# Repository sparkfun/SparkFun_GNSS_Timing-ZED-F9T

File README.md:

SparkFun GNSS Timing Breakout - ZED-F9T (Qwiic)
========================================

[*SparkFun GNSS Timing Breakout - ZED-F9T (Qwiic) (GPS-18774)*](https://www.sparkfun.com/products/18774)

The SparkFun GNSS Timing Breakout - ZED-F9T (Qwiic) offers a unique entry into SparkFun&apos;s GNSS catalog featuring the ZED-F9T GNSS receiver from u-blox. The ZED-F9T provides up to 5 nanosecond timing accuracy under clear skies with no external GNSS correction. The ZED-F9T supports L1/L2 bands and operates on all major constellations concurrently so it is able to maintain its timing precision even if the module loses connection with on or more of the visible constellations.

The breakout includes a USB-C connector for primary power and communication, two Qwiic connectors for communicating over I<sup>2</sup>C using the SparkFun [Qwiic system](https://www.sparkfun.com/qwiic), three SMA connectors for the antenna and timing pulse signals as well as a host of PTH pins allowing direct interaction with most of the ZED-F9T's pinout. The board also includes an on-board rechargeable battery that provides power to the RTC on the ZED-F9T. This reduces the time-to-first fix from a cold start (~24s) to a hot start (~2s). 

Repository Contents
-------------------

* **/Documents** - Datasheet, Appnotes.
* **/Hardware** - Eagle design files (.brd, .sch)

Documentation
-------------

* **[SparkFun u-blox GNSS Arduino Library](https://github.com/sparkfun/SparkFun_u-blox_GNSS_Arduino_Library)** - A comprehensive library for all SparkFun u-blox products.
* **[Hookup Guide](https://learn.sparkfun.com/tutorials/gnss-timing-breakout---zed-f9t-qwiic-hookup-guide)** - A basic Hookup Guide to get started with the SparkFun GNSS Timing Breakout - ZED-F9T (Qwiic).

Product Versions
----------------
* [GPS-18774](https://www.sparkfun.com/products/18774) - Initial release

Version History
---------------
* v1.0 - Initial Release 

License Information
-------------------

This product is _**open source**_! 

Please review the LICENSE.md file for license information. 

If you have any questions or concerns on licensing, please contact technical support on our [SparkFun forums](https://forum.sparkfun.com/viewforum.php?f=152).

Distributed as-is; no warranty is given.

- Your friends at SparkFun.

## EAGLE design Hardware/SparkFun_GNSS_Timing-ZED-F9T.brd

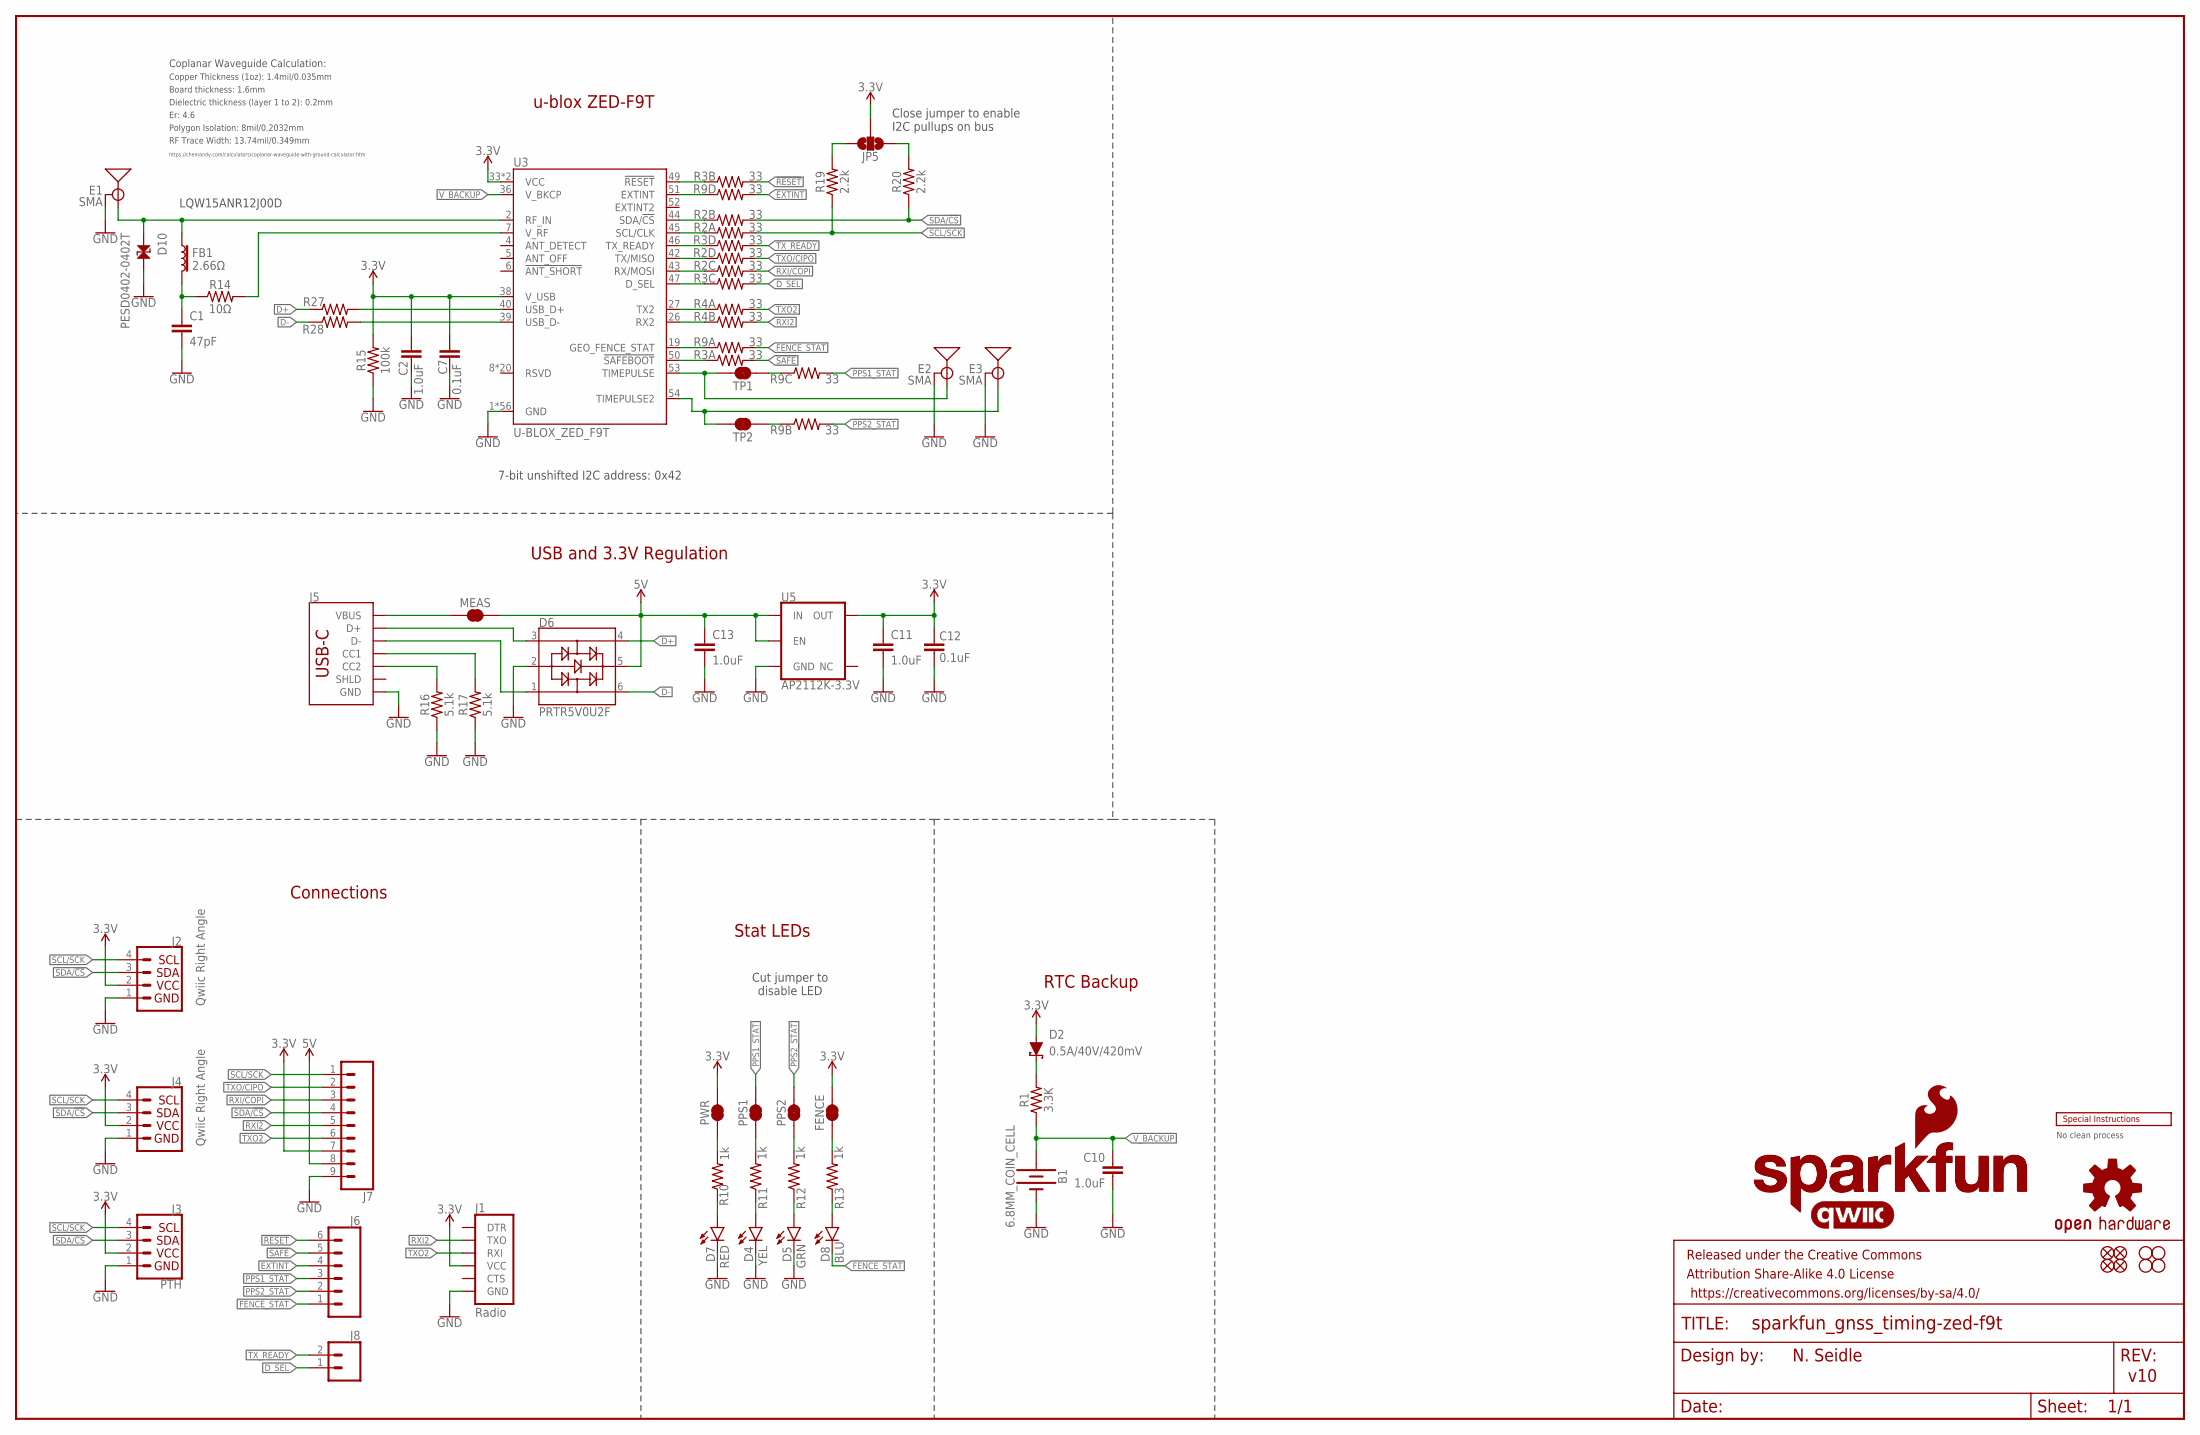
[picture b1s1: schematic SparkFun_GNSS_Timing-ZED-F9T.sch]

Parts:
B1: 6.8MM_COIN_CELL; ML414H_IV01E
C1: 47pF; 0402-TIGHT
C2, C10, C11, C13: 1.0uF; 0402-TIGHT
C7, C12: 0.1uF; 0402-TIGHT
D2: 0.5A/40V/420mV; SOD-323
D4: YEL; LED-0603
D5: GRN; LED-0603
D6: PRTR5V0U2F; SOT886
D7: RED; LED-0603
D8: BLU; LED-0603
D10: PESD0402-0402T; 0402-TIGHT
E1, E2, E3: SMA; SMA-EDGE
FB1: 2.66Ω; 0402-TIGHT
FENCE: JUMPER-SMT_2_NC_TRACE_SILK; SMT-JUMPER_2_NC_TRACE_SILK
FRAME2: FRAME-LEDGER; CREATIVE_COMMONS
H1, H2, H3, H4: STAND-OFF
J1: Radio; 1X06_NO_SILK
J2, J4: Qwiic Right Angle; JST04_1MM_RA
J3: PTH; 1X04_NO_SILK
J5: USB Female Type C Connector; USB-C-16P_4LAYER-PADS
J6: CONN_06NO_SILK_FEMALE_PTH; 1X06_NO_SILK
J7: CONN_09NO_SILK; 1X09_NO_SILK
J8: CONN_021X02_NO_SILK; 1X02_NO_SILK
JP5: JUMPER-SMT_3_NO_SILK; SMT-JUMPER_3_NO_SILK
JP21, JP61, JP71, JP81: FIDUCIALUFIDUCIAL; FIDUCIAL-MICRO
LOGO1: OSHW-LOGOMINI; OSHW-LOGO-MINI
LOGO2: SFE_LOGO_NAME_FLAME.1_INCH; SFE_LOGO_NAME_FLAME_.1
LOGO4: QWIIC_LOGO_4MM; QWIIC_4MM
LOGO5: SFE_LOGO_NAME.1_INCH; SFE_LOGO_NAME_.1
MEAS: JUMPER-COMBO_2_NC_TRACE; COMBO-JUMPER_2_NC_TRACE
PPS1, PPS2: JUMPER-SMT_2_NC_TRACE_SILK; SMT-JUMPER_2_NC_TRACE_SILK
PWR: JUMPER-SMT_2_NC_TRACE_SILK; SMT-JUMPER_2_NC_TRACE_SILK
R1: 3.3K; 0402-TIGHT
R2, R3, R4, R9: 33; 1206_RA
R10, R11, R12, R13: 1k; 0402-TIGHT
R14: 10Ω; 0402-TIGHT
R15: 100k; 0402-TIGHT
R16, R17: 5.1k; 0402-TIGHT
R19, R20: 2.2k; 0402-TIGHT
R27, R28: 27OHM; 0402-TIGHT
TP1, TP2: JUMPER-SMT_2_NC_TRACE_SILK; SMT-JUMPER_2_NC_TRACE_SILK
U3: U-BLOX_ZED_F9T; ZED-F9X
U5: AP2112K-3.3V; SOT23-5
U$2: SPECIAL_INSTRUCTIONS-ORDERING; ORDERING_INSTRUCTIONS

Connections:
3.3V: C2.1, C7.2, C11.1, C12.2, D2.A, FENCE.2, J1.4 (VCC), J2.2, J3.2 (VCC), J4.2, J7.7, JP5.2, PWR.2, R15.2, U3.33 (VCC), U3.34 (VCC), U3.38 (V_USB), U5.5 (OUT)
5V: C13.1, D6.5, J7.8, MEAS.2, MEAS.4 (2), U5.1 (IN), U5.3 (EN)
!RESET!: J6.6, R3.P7 (2)
!RESET!_LV: R3.P2 (1), U3.49 (!RESET!)
!SAFE!: J6.5, R3.P8 (2)
!SAFE!_LV: R3.P1 (1), U3.50 (!SAFEBOOT!)
ANT_VCC: C1.1, FB1.2, R14.1
CC1: J5.A5 (CC1), R17.2
CC2: J5.B5 (CC2), R16.2
D+: D6.4, R27.1
D-: D6.6, R28.1
DSEL_LV: R3.P3 (1), U3.47 (D_SEL)
D_SEL: J8.1, R3.P6 (2)
EXTINT: J6.4, R9.P5 (2)
EXTINT_LV: R9.P4 (1), U3.51 (EXTINT)
FENCE_LV: R9.P1 (1), U3.19 (GEO_FENCE_STAT)
FENCE_STAT: D8.C, J6.1, R9.P8 (2)
GND: B1.-, C1.2, C2.2, C7.1, C10.2, C11.2, C12.1, C13.2, D4.C, D5.C, D6.2, D7.C, D10.2, E1.GND@0 (GND), E1.GND@1 (GND), E1.GND@2 (GND), E1.GND@3 (GND), E2.GND@0 (GND), E2.GND@1 (GND), E2.GND@2 (GND), E2.GND@3 (GND), E3.GND@0 (GND), E3.GND@1 (GND), E3.GND@2 (GND), E3.GND@3 (GND), J1.6 (GND), J2.1, J3.1 (GND), J4.1, J5.GND, J5.GND2 (GND), J7.9, R15.1, R16.1, R17.1, U3.1 (GND), U3.3 (GND), U3.12 (GND), U3.14 (GND), U3.32 (GND), U3.37 (GND), U3.41 (GND), U3.48 (GND), U3.G1 (GND), U3.G2 (GND), U3.G3 (GND), U3.G4 (GND), U3.G5 (GND), U3.G6 (GND), U3.G7 (GND), U3.G8 (GND), U3.G9 (GND), U3.G10 (GND), U3.G11 (GND), U3.G12 (GND), U3.G13 (GND), U3.G14 (GND), U3.G15 (GND), U3.G16 (GND), U3.G17 (GND), U3.G18 (GND), U3.G19 (GND), U3.G20 (GND), U3.G21 (GND), U3.G22 (GND), U3.G23 (GND), U3.G24 (GND), U3.G25 (GND), U3.G26 (GND), U3.G27 (GND), U3.G28 (GND), U3.G29 (GND), U3.G30 (GND), U3.G31 (GND), U3.G32 (GND), U3.G33 (GND), U3.G34 (GND), U3.G35 (GND), U3.G36 (GND), U3.G37 (GND), U3.G38 (GND), U3.G39 (GND), U3.G40 (GND), U3.G41 (GND), U3.G42 (GND), U3.G43 (GND), U3.G44 (GND), U3.G45 (GND), U3.G46 (GND), U3.G47 (GND), U3.G48 (GND), U5.2 (GND)
GPS_ANT1: D10.1, E1.SIG (SIGNAL), FB1.1, U3.2 (RF_IN)
unnamed: D4.A, R11.1
unnamed: PPS1.1, R11.2
unnamed: J5.VBUS1 (VBUS), J5.VBUS2 (VBUS), MEAS.1, MEAS.3 (1)
unnamed: R9.P3 (1), TP1.1
unnamed: D2.C, R1.2
unnamed: R9.P2 (1), TP2.1
unnamed: R27.2, U3.40 (USB_D+)
unnamed: R28.2, U3.39 (USB_D-)
unnamed: R14.2, U3.7 (V_RF)
unnamed: D7.A, R10.1
unnamed: D5.A, R12.1
unnamed: PPS2.1, R12.2
unnamed: D8.A, R13.1
unnamed: FENCE.1, R13.2
unnamed: PWR.1, R10.2
unnamed: JP5.1, R20.2
unnamed: JP5.3, R19.2
PPS1_STAT: J6.3, PPS1.2, R9.P6 (2)
PPS2_STAT: J6.2, PPS2.2, R9.P7 (2)
RX1_LV: R2.P3 (1), U3.43 (RX/MOSI)
RX2_LV: R4.P2 (1), U3.26 (RX2)
RXI2: J1.3 (TXO), J7.5, R4.P7 (2)
RXI/COPI: J7.3, R2.P6 (2)
SCL/SCK: J2.4, J3.4 (SCL), J4.4, J7.1, R2.P8 (2), R19.1
SCL_LV: R2.P1 (1), U3.45 (SCL/CLK)
SDA/!CS: J2.3, J3.3 (SDA), J4.3, J7.4, R2.P7 (2), R20.1
SDA_LV: R2.P2 (1), U3.44 (SDA/!CS!)
TP1_LV: E2.SIG (SIGNAL), TP1.2, U3.53 (TIMEPULSE)
TP2_LV: E3.SIG (SIGNAL), TP2.2, U3.54 (TIMEPULSE2)
TX1_LV: R2.P4 (1), U3.42 (TX/MISO)
TX2_LV: R4.P1 (1), U3.27 (TX2)
TXO2: J1.2 (RXI), J7.6, R4.P8 (2)
TXO/CIPO: J7.2, R2.P5 (2)
TX_READY: J8.2, R3.P5 (2)
TX_READY_LV: R3.P4 (1), U3.46 (TX_READY)
UNP_D+: D6.3, J5.A6 (D+), J5.B6 (D+)
UNP_D-: D6.1, J5.A7 (D-), J5.B7 (D-)
V_BACKUP: B1.+, C10.1, R1.1, U3.36 (V_BKCP)

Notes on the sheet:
v10
7-bit unshifted I2C address: 0x42
u-blox ZED-F9T
LQW15ANR12J00D
Board thickness: 1.6mm
Er: 4.6
Copper Thickness (1oz): 1.4mil/0.035mm
RF Trace Width: 13.74mil/0.349mm
Polygon Isolation: 8mil/0.2032mm
No clean process
Dielectric thickness (layer 1 to 2): 0.2mm
https://chemandy.com/calculators/coplanar-waveguide-with-ground-calculator.htm
Coplanar Waveguide Calculation:
USB and 3.3V Regulation
N. Seidle
Cut jumper to disable LED
RTC Backup
Close jumper to enable I2C pullups on bus
Stat LEDs
Connections

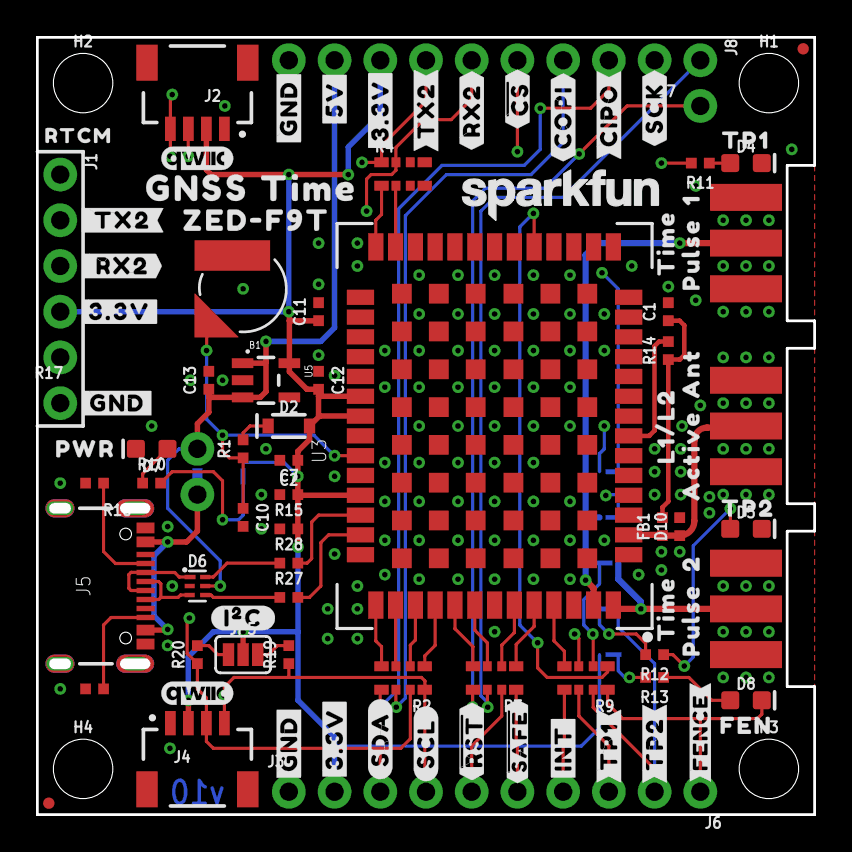
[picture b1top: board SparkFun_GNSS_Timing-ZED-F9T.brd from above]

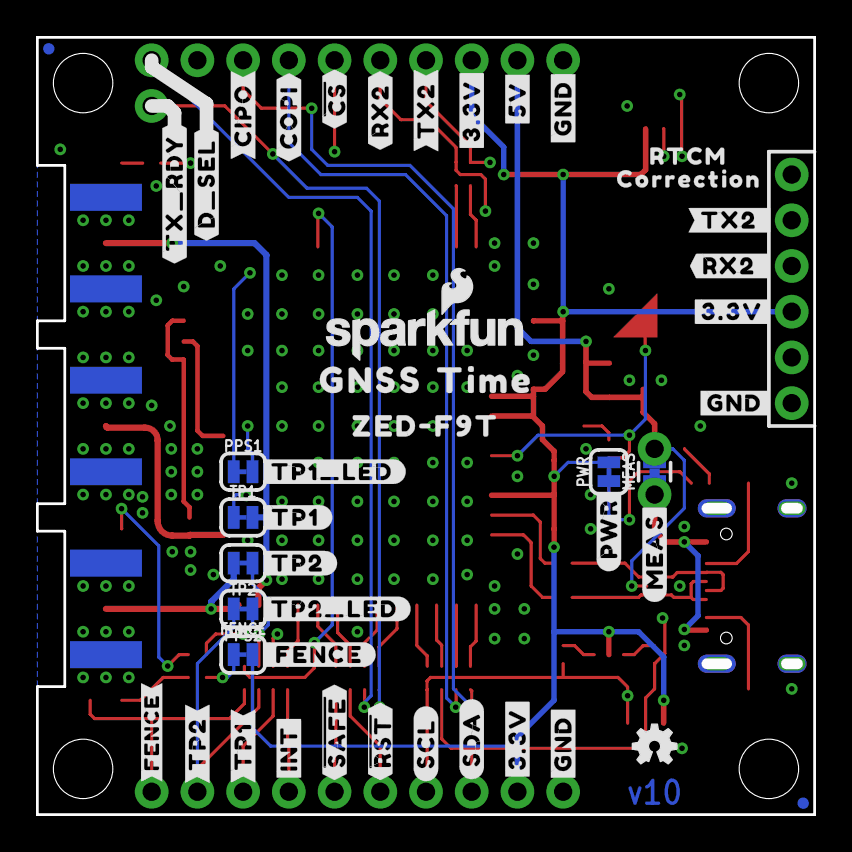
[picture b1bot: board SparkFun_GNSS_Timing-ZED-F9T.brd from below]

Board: 4 copper layers, 43.2 x 43.2 mm, 146 parts (47 on the bottom side), 57 nets.

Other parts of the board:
LOGO3: QWIIC_LOGO_4MM; QWIIC_4MM
U$1, U$29, U$35, U$36, U$59, U$60: #3#3V#0
U$3, U$28: #5V#1
U$4, U$27, U$38, U$39, U$61, U$62: #GND#2
U$5, U$8: ##CS##4
U$6: L1#L20
U$7, U$21: TIME0
U$9, U$10: #CIPO#6
U$11, U$12: #COPI#5
U$13: ACTIVE1
U$14, U$16: #RX2#1
U$15, U$37: ##RST##0
U$17, U$53: #SCL#3
U$18, U$22: #SDA#2
U$19, U$25: PULSE1
U$20: 12
U$23, U$24: #TX2#0
U$26: 20
U$30: #SCK#5
U$31: ANT1
U$32: #_TX2#0
U$33: #D_SEL#1
U$34, U$77: ZED#F9T0
U$40, U$70: GNSS0
U$41: ##SAFE##1
U$42, U$43: #INT#2
U$44, U$65: #FENCE#0
U$45: #TP2_LED#0
U$46, U$47: #TP1#3
U$48, U$49: #TP2#4
U$50: #TP2#0
U$51: #_FENCE#0
U$52: #TP1#0
U$54: #TP1_LED#0
U$55: #_RX2#0
U$56: PWR0
U$57: #PWR#0
U$58: #RX2_#0
U$63: TP10
U$64: TP21
U$66: #TX2_#0
U$67: #TX_RDY#0
U$68: #MEAS#0
U$69: #I�C#0
U$71, U$74: TIME1
U$72: ##SAFE##0
U$73: RTCM0
U$75: CORRECTION1
U$76: RTCM_0
U$78: FEN0

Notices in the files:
parts and their libraries:
SparkFun-Resistors: Licensing: Creative Commons ShareAlike 4.0 International - https://creativecommons.org/licenses/by-sa/4.0
SparkFun-Aesthetics: Released under the Creative Commons Attribution Share-Alike 4.0 License
SparkFun-Aesthetics: https://creativecommons.org/licenses/by-sa/4.0
